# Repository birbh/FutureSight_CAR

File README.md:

# FutureSight_CAR:
FutureSight is an automotive dashcam built from scratch from Milk-V Duo S. It features hardware accelerated 1680p continuous loop recording with an 12c G-sensor for auto crash detection. Also I have prepared a custom 12 volt to 5 volt power converting board to handle the non sturdy vehicle(car) power.

## What makes it unique??
Unlike the commercial dashcams that lock footage behind their own apps. This project gives a person complete access and ownership of hardware and software stack. It runs a raw python on RISC-V Linux env. The hardware stack si built for extreme durability, utilizing a TPS54360DDA bulk converter and a 5.5V 4.0F supercapacitor for safe shutdown and giving time to save files before car switches off. Also it is designed to manage heat efficiently by using the large heat sync in the back panel and go-pro style mounting hinge so that it can be rotated to any angle. 

## Why i made it?
Recently my father's car got into an accident and he paid the damaged repairing cost although it wasn't his fault. So from that day i thought it would be cool if we get a dashcam(a good one). But after seeing the dashcams online the good ones were so expensive. So i thought why not make my own dashcam in home. Also i thought driving a car in those busy and chaotic roads of Kathmandu would be easier and feel confident because everything you and other person do is fully recorded and also helps us to be in discipline cause we think that this all is being recorded and we are bound to laws. 

## How to use it?
1. Mount+wire:
  Attach the dashcam module(assembled) to your car windshield using gopro compatible mount provided in 3d files of repo. Then wire 2 pin screw terminal on pcb directly to 12V power source in your car sing a cigarette lighter adapter for car.

2. Starting dashcam:
  Turn on your car. Then the system boots automatically and providing power to Milk-v-duo S. Then a background service immediately starts recording a video in 3 min. chunks.

3. Storage management:
  When the microsd card fills up, the software automatically deletes oldest normal driving footage.

4. Smart impact protection:
  If the MPU-6050 accelerometer chip detects a sudden G-force spike(triggered by eg:: hard braking, collision, car slipping etc.) , then the current video is instantly locked into `/events/` folder in sd card where it can't be overwritten. Otherwise if you press a button in the back of the dashcam it will be auto saved to `/events/` folder. Other normal recordings are saved to `/normal` folder.

## Assembly Instructions:
### 3d print enclosure:
All te 3d CAD files are provided in CAD folder of this repo. And especially 3d printable parts can be found on `/CAD/3d print/` folder in this repo. Use a high tempetrature resistant filament profile like ABS or ASA. Don't use PLA or PETG as they are not so resistant to heat and can melt on car interior temp. as it easily reaches about 70-80 °C in summer season. Also all the mounts have been pre defined in the CAD so there is no need to worry for screw fitting. 

### PCB and soldering:
Fabricate the custom matte black Kicad Pcb. Solder the SMD components first paying special attention to all components. Also before pcb printing check the 12v-5v power lines are of 1-1.5 mm width. Then solder the all the required parts to their respective footprints and places. Also snap the Milk-v-Duo S to its respective place J1 And J2 same as shown in 3d CAD model. Please ensure all the pins are arranged with the pcb otherwise it will not function. Also note that the upper black thing is completely optional because they are just pin headers that are add in 3d model. 

### Mounting:
I have provided each and every screw slots in the 3d model so that each component easily fits into the enclosure. Also dont forget to connect the camera to the milk-v duo s connector cause without camera the system is nothing. To mount camera you must take the lid side and mount the screws into it s that camera stays fit in it. 

### Flashing firmware:
Flash the official MIlk-V OS image into your SDcard. Then connect them via onboard micro sd adapter and install the required dependencies(ffmpeg,python3,py3-smbus2). Create `/mnt/sdcard/dashcam/normal/` and `/mnt/sdcard/dashcam/events/` folder/directories inside the sd card. Drop the firmware files in the root folder and enable it as a startup service. 

### Getting the data:
For now you can extract your dashcam videos by unplugging the Sd-card from the dashcam and plugging it in the sd card reader in pc,mobile or any other mountable device. And also you can directly connect your milk v type c port into your pc and access your data. But in future i plan to make a native app for the dashcam and use the inbuilt wifi antenna thing to sync the data. Also i plan to make the app fully run locally in users’ devices, protecting the privacy of the user.  

## Milk-V Duo S setup(in detail):
Once your Pcb is soldered and milk-v duo-s is mounted, follow these steps to configure dashcam:::

1. Flash the OS:
  - Download the official Milk-V Duo S Linux image from milk v [Github repo](https://github.com/milkv-duo/duo-buildroot-sdk-v2/releases)
  - then flash the image to a micros card using tools like Rufus or balenaEtcher or any other image flashing software.
  - insert the micro sd card into duo s and power it using the USB-C port(note: don't apply the car 12V power yet.)

2. Install the required drivers:
  i. For Windows users:
    Windows often fails to recognize the board automatically. You need to tell it to treat the USB connection as a network card.
    - Open Device Manager: Look under Other devices for an unknown device (often labeled Serial or RNDIS).
    - Update Driver: Right-click it, select Update driver, and choose Browse my computer for drivers.
    - Select from List: Click Let me pick from a list of available drivers on my computer.
    - Choose Network Adapters: Select Network adapters from the list, choose Microsoft as the manufacturer, and select Remote NDIS Compatible Device (or USB RNDIS Adapter).
    - Finish: Click Next and ignore any warning prompts.
    
  ii. For macos/Linux users:
    Linux and Mac usually recognize the RNDIS interface automatically, but you need to check if the network interface is active.
    - Open Terminal: Run ip a (Linux) or ifconfig (Mac).
    - Look for a new interface: You should see a new network interface (usually named something like usb0 or enX).
    
3. Setup SSH into the board:
  - Connect the Milk-V Duo S into your computer after installing required drivers.It will mount as a virtual network adapter(RNDIS).
  - Open your terminal and SSH into your default IP adress `192.168.42.1`.
  - ```bash
    ssh root@192.168.42.1
    ```
  - the default password is typically `milkv`

4. Install dependencies:
  Depending on specific os image you flashed, use the system package manager to install reqd video and python packages:
  - ```bash
    apt-get update
    sudo apt install ffmpeg
    sudo apt install python3 python3-pip
    pip3 install smbus2
    ```
5. Create the required storage directories:
  - ```bash
    mkdir -p/mnt/sdcard/dashcam/normal/
    mkdir -p/mnt/sdcard/dashcam/events/
    
6. Transfer the python script(firmware):
  From your computer use SCP(secure copy) protocol to transfer your finalized firmware firmware.py script into root folder of Milk-V Duo S:
  ```bash
scp firmware.py root@192.168.42.1:/root/
```

7. Create auto-start service when boot:
   The dashcam must boot on its own when car turns on. So use systemd to make script aut run in the bg:
   - Create the service file:
   ```bash
   vi /etc/systemd/system/dashcam.service
   ```
   - Paste the exact configuration into the file:
   ```bash
      [Unit]
      Description=Dashcam Auto recors svc
      After=systemd-modules-load.service
      
      [Service]
      Type=simple
      ExecStart=/usr/bin/python3 /root/firmware.py
      Restart=always
      RestartSec=3
      
      [Install]
      WantedBy=multi-user.target
   ```
  - Save the file and exit.

8. Enable and test:
  - Enable the service so it starts automatically on every boot.Also start manually to test it now:
    ```bash
    systemctl enable dashcam.service
    systemctl start dashcam.service
    ```
  - Verify that the camera is recording and G-sensor is polling by checking the status:
    ```bash
    systemctl status dashcam.service
    ```
  - Now at this point the usb-c cable can be disconnected and your dashcam is ready to be mounted inside the car Cigarette Lighter 12V port.... YAYYYYYY!!! les goooooooo!! 

## Future changes:
I have kept the ipex connector cable with wifi+bluetooth antenna in the pcb,BOM and CAD but that is completely optional for now as the app and the wifi setup hasnt been added in the firmware yet. In future it will be added. Also the app for the dashcam isnt functional yet and will be updated in future.

## Assets:
### CAD screenshots:

### CAD link:
[Fusion Link](https://a360.co/47AANnS)

### PCB screenshots:

### Schematic:
1. Power Control:

2. Safe shut

3. Duos_interface:

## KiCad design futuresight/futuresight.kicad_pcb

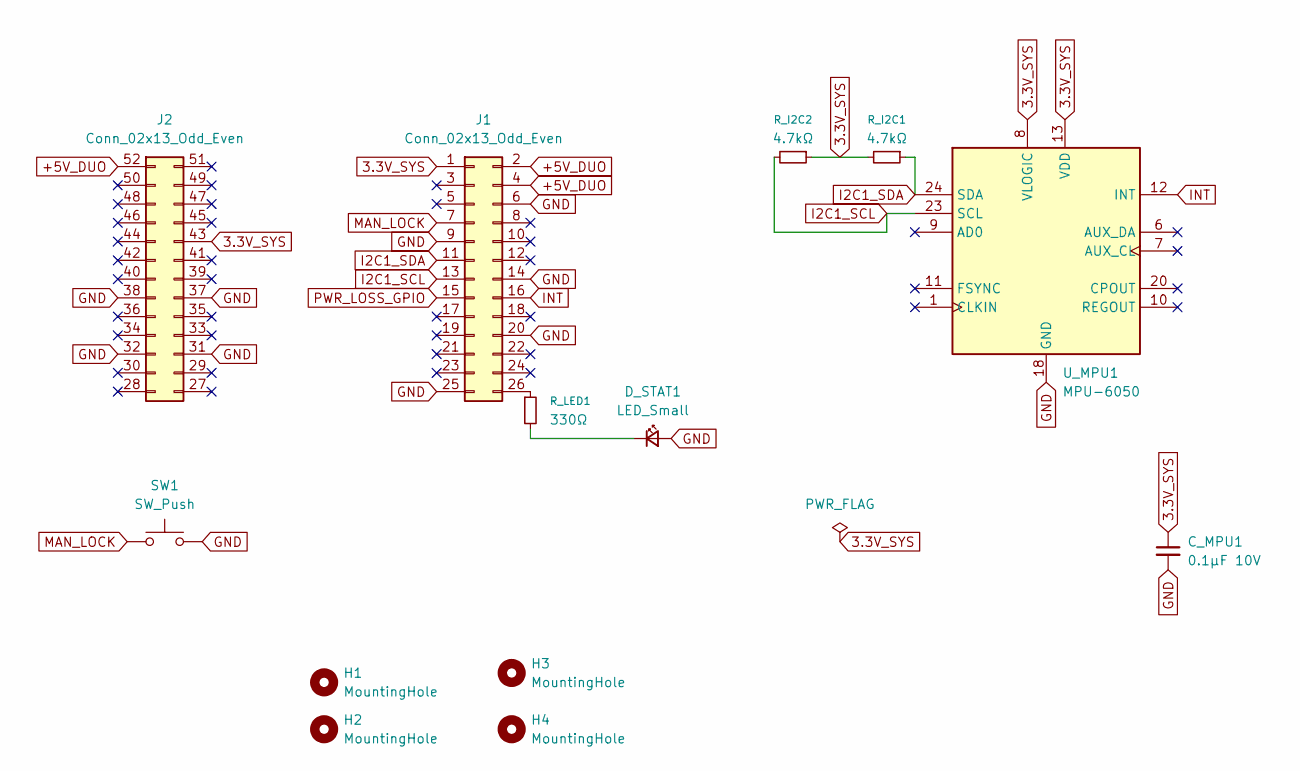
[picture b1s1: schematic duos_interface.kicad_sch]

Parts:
C_MPU1: 0.1µF 10V; C_0603_1608Metric_Pad1.08x0.95mm_HandSolder
D_STAT1: LED_Small; LED_0603_1608Metric_Pad1.05x0.95mm_HandSolder
H1, H2, H3, H4: MountingHole; MountingHole_2.7mm_M2.5
J1, J2: Conn_02x13_Odd_Even; PinSocket_2x13_P2.54mm_Vertical
R_I2C1, R_I2C2: 4.7kΩ; R_0603_1608Metric_Pad0.98x0.95mm_HandSolder
R_LED1: 330Ω; R_0603_1608Metric_Pad0.98x0.95mm_HandSolder
SW1: SW_Push; SW_SPST_B3S-1000
U_MPU1: MPU-6050; InvenSense_QFN-24_4x4mm_P0.5mm

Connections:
3.3V_SYS: C_MPU1.1, J1.1, J2.43, R_I2C1.2, R_I2C2.1, U_MPU1.8 (VLOGIC), U_MPU1.13 (VDD)
+5V_DUO: J1.2, J1.4, J2.52; also elsewhere on the board
GND: C_MPU1.2, D_STAT1.2 (A), J1.6, J1.9, J1.14, J1.20, J1.25, J2.31, J2.32, J2.37, J2.38, SW1.2, U_MPU1.18 (GND); also elsewhere on the board
I2C1_SCL: J1.13, R_I2C2.2, U_MPU1.23 (SCL)
I2C1_SDA: J1.11, R_I2C1.1, U_MPU1.24 (SDA)
INT: J1.16, U_MPU1.12 (INT)
MAN_LOCK: J1.7, SW1.1
unnamed: D_STAT1.1 (K), R_LED1.2
unnamed: J1.26, R_LED1.1
PWR_LOSS_GPIO: J1.15; also elsewhere on the board

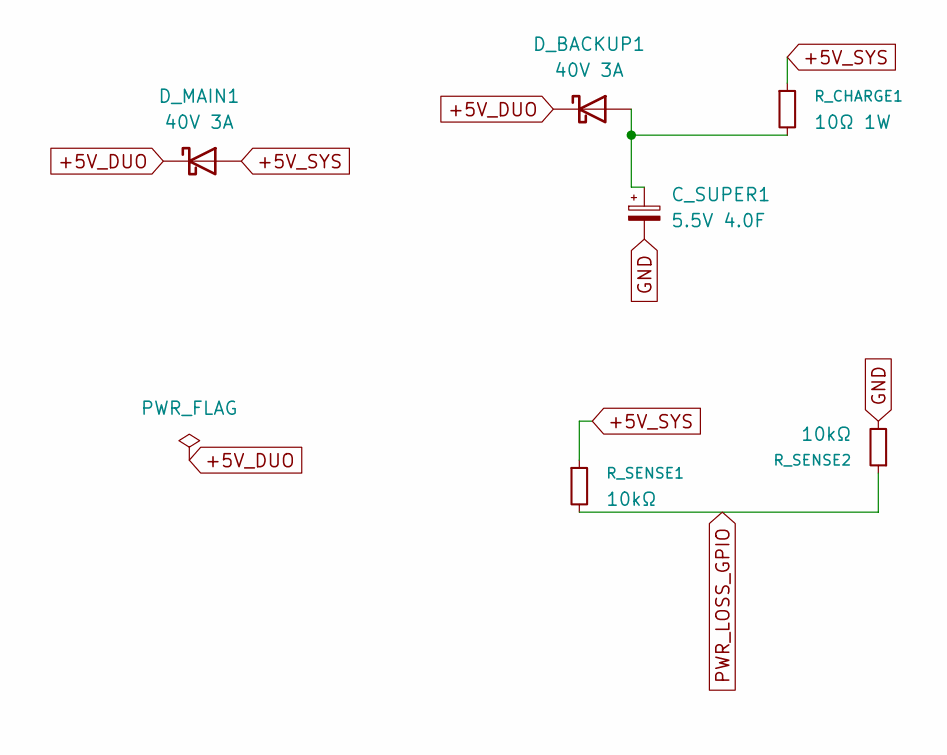
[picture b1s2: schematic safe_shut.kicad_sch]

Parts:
C_SUPER1: 5.5V 4.0F; CP_Radial_D24.0mm_P10.00mm_SnapIn
D_BACKUP1: 40V 3A; D_SMC_Handsoldering
D_MAIN1: 40V 3A; D_SMC_Handsoldering
R_CHARGE1: 10Ω 1W; R_2512_6332Metric_Pad1.40x3.35mm_HandSolder
R_SENSE1, R_SENSE2: 10kΩ; R_0603_1608Metric_Pad0.98x0.95mm_HandSolder

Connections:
+5V_DUO: D_BACKUP1.1 (K), D_MAIN1.1 (K); also elsewhere on the board
+5V_SYS: D_MAIN1.2 (A), R_CHARGE1.1, R_SENSE1.1; also elsewhere on the board
GND: C_SUPER1.2, R_SENSE2.2; also elsewhere on the board
unnamed: C_SUPER1.1, D_BACKUP1.2 (A), R_CHARGE1.2
PWR_LOSS_GPIO: R_SENSE1.2, R_SENSE2.1; also elsewhere on the board

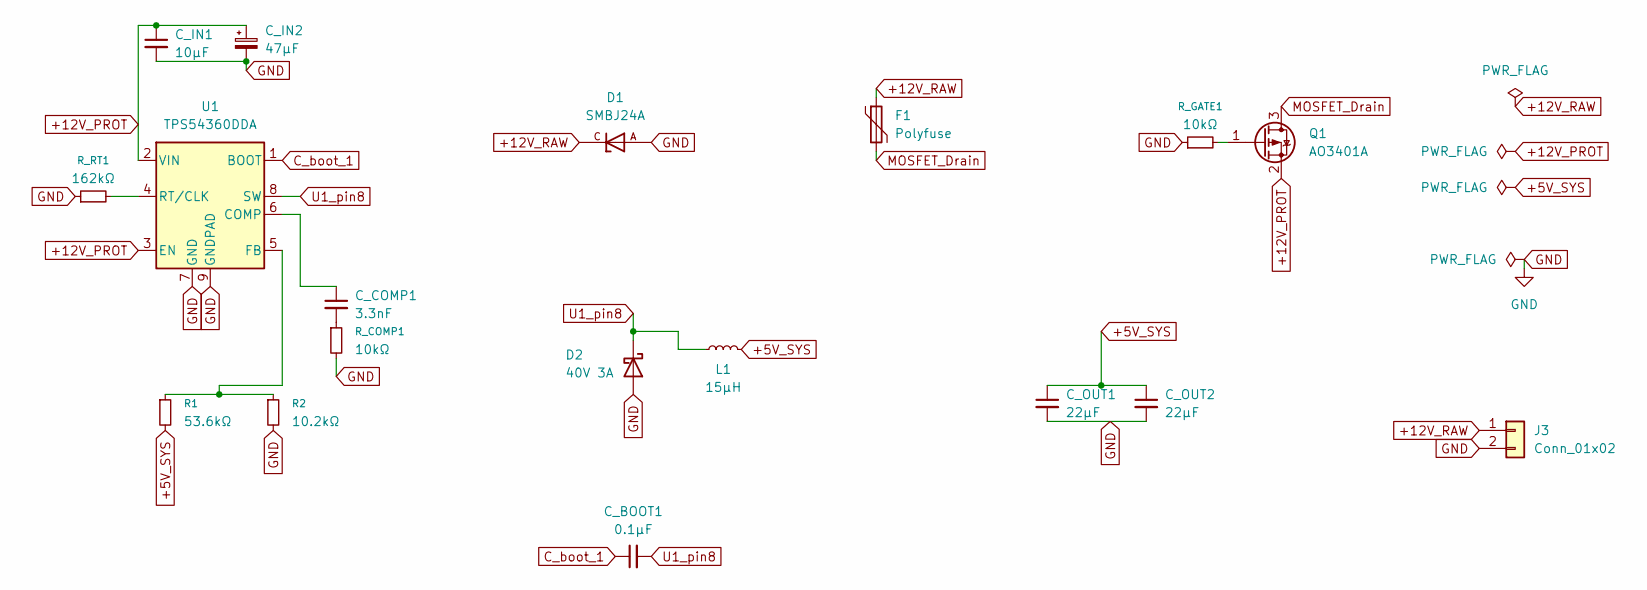
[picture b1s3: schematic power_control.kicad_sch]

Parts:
C_BOOT1: 0.1µF; C_0603_1608Metric_Pad1.08x0.95mm_HandSolder
C_COMP1: 3.3nF; C_0603_1608Metric_Pad1.08x0.95mm_HandSolder
C_IN1: 10µF; C_1206_3216Metric_Pad1.33x1.80mm_HandSolder
C_IN2: 47µF; CP_Elec_6.3x5.8
C_OUT1, C_OUT2: 22µF; C_1206_3216Metric_Pad1.33x1.80mm_HandSolder
D1: SMBJ24A; DIOM4336X265N; PARTREV F2102
D2: 40V 3A; D_SMA_Handsoldering
F1: Polyfuse; Fuse_1812_4532Metric_Pad1.30x3.40mm_HandSolder
J3: Conn_01x02; TerminalBlock_Phoenix_MKDS-1,5-2-5.08_1x02_P5.08mm_Horizont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
L1: 15µH; L_Bourns-SRN8040_8x8.15mm
Q1: AO3401A; SOT-23
R1: 53.6kΩ; R_0603_1608Metric_Pad0.98x0.95mm_HandSolder
R2: 10.2kΩ; R_0603_1608Metric_Pad0.98x0.95mm_HandSolder
R_COMP1: 10kΩ; R_0603_1608Metric_Pad0.98x0.95mm_HandSolder
R_GATE1: 10kΩ; R_0603_1608Metric_Pad0.98x0.95mm_HandSolder
R_RT1: 162kΩ; R_0603_1608Metric_Pad0.98x0.95mm_HandSolder
U1: TPS54360DDA; TI_SO-PowerPAD-8_ThermalVias

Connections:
+5V_SYS: C_OUT1.1, C_OUT2.1, L1.2, R1.2; also elsewhere on the board
+12V_PROT: C_IN1.1, C_IN2.1, Q1.2 (S), U1.2 (VIN), U1.3 (EN)
+12V_RAW: D1.C, F1.1, J3.1
C_boot_1: C_BOOT1.1, U1.1 (BOOT)
GND: C_IN1.2, C_IN2.2, C_OUT1.2, C_OUT2.2, D1.A, D2.2 (A), J3.2, R2.2, R_COMP1.2, R_GATE1.1, R_RT1.1, U1.7 (GND), U1.9 (GNDPAD); also elsewhere on the board
MOSFET_Drain: F1.2, Q1.3 (D)
unnamed: C_COMP1.2, R_COMP1.1
unnamed: Q1.1 (G), R_GATE1.2
unnamed: C_COMP1.1, U1.6 (COMP)
unnamed: R1.1, R2.1, U1.5 (FB)
unnamed: R_RT1.2, U1.4 (RT/CLK)
U1_pin8: C_BOOT1.2, D2.1 (K), L1.1, U1.8 (SW)

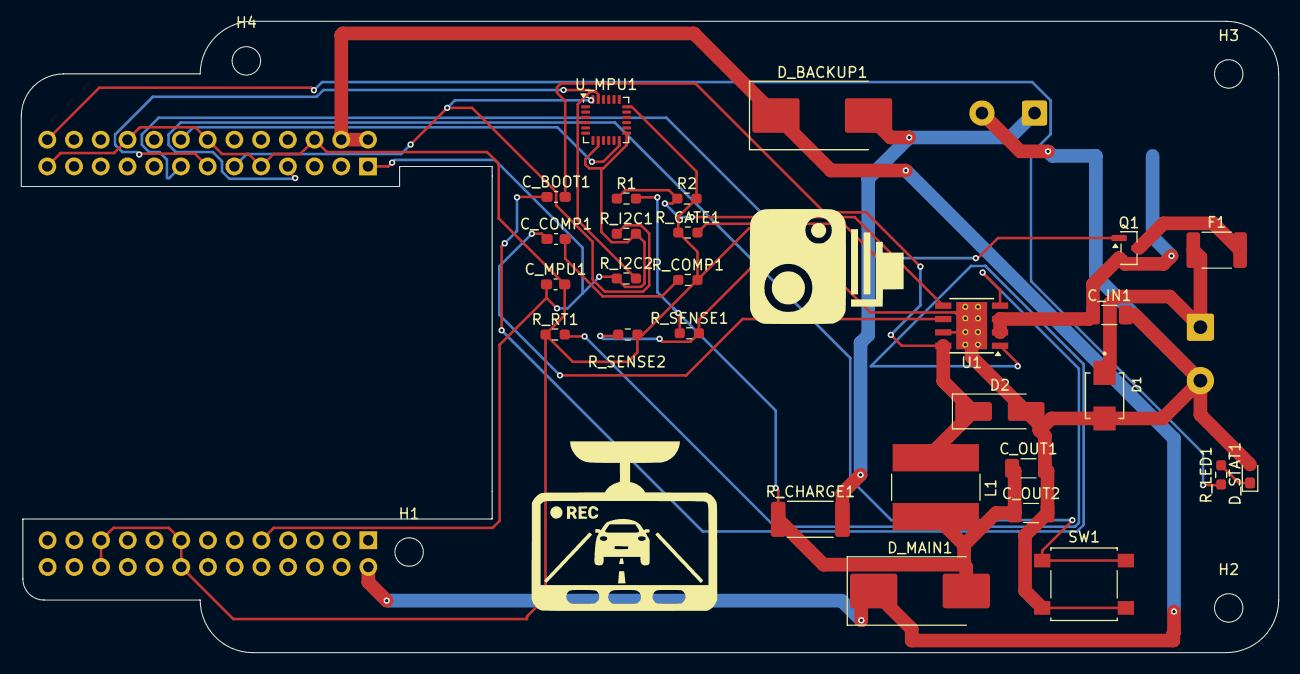
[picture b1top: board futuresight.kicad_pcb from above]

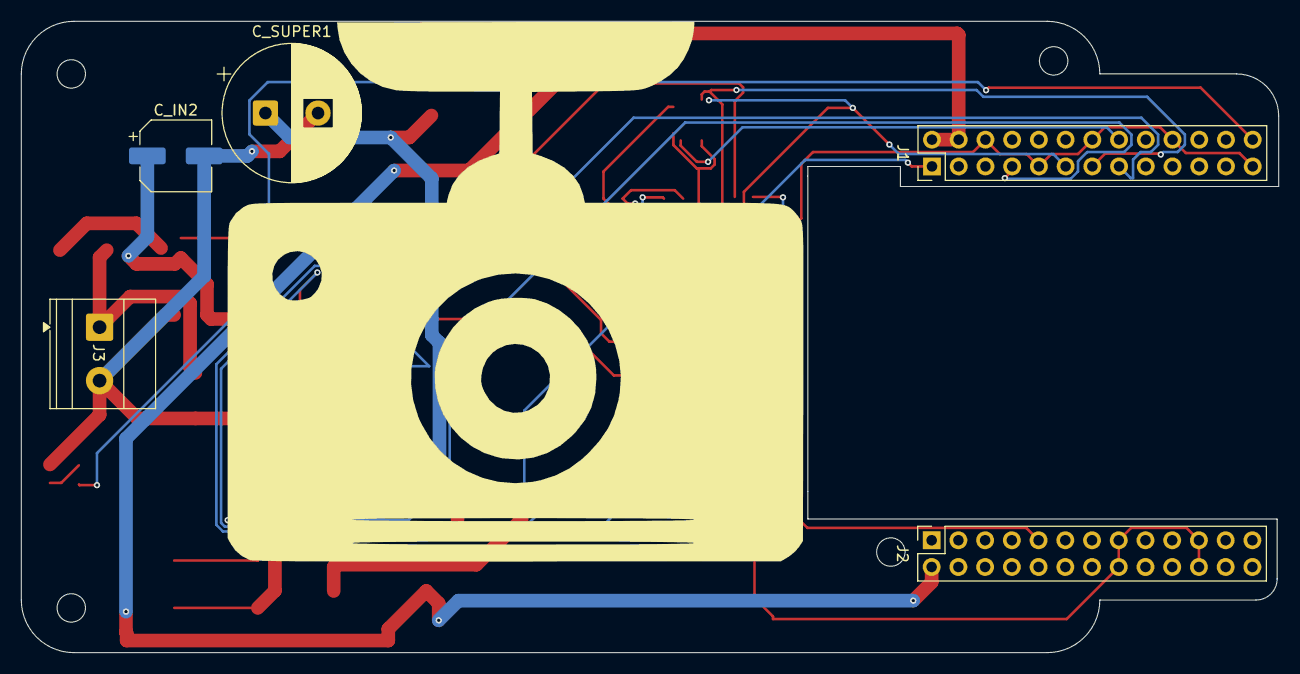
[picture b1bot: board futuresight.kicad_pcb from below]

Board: 2 copper layers, 119.5 x 60.0 mm, 37 parts (5 on the bottom side), 22 nets.
